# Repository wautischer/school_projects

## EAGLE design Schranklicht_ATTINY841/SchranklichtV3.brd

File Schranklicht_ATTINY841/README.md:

# Schranklicht
## Used Parts:
[partlist.txt](https://github.com/wautischer/Schranklicht/files/15400422/partlist.txt)
## Circuit:

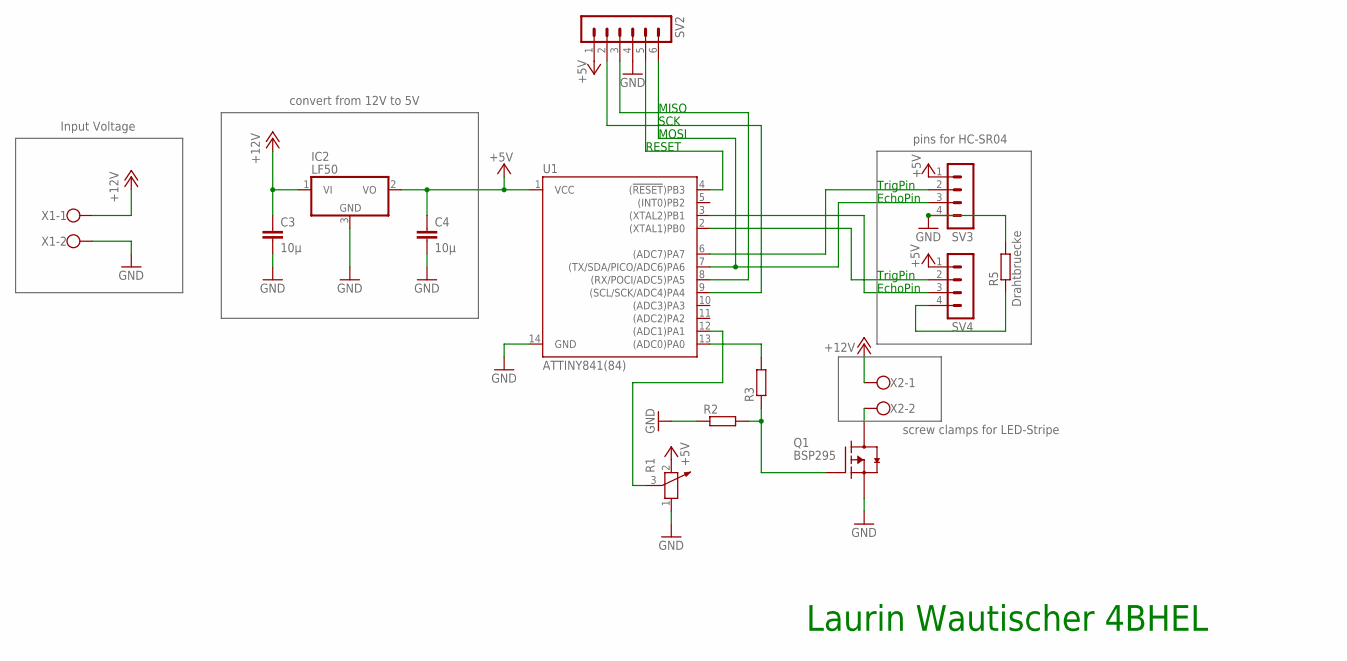
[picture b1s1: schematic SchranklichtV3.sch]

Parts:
C3, C4: 10µ; C1210
IC2: LF50; TO252
Q1: BSP295; SOT230P700X160-4N
R1: POTENTIOMETER_PT-10; PT-10
R2, R3: R-EU_0207/10; 0207/10
R5: Drahtbruecke; 0207/7
SV2: MA06-1
SV3, SV4: MA04-1
U1: ATTINY841(84); SO14
X1, X2: W237-102

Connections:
+5V: C4.1, IC2.2 (VO), R1.2, SV2.1, SV3.1, SV4.1, U1.1 (VCC)
+12V: C3.1, IC2.1 (VI), X1.1, X2.1
GND: C3.2, C4.2, IC2.3 (GND), Q1.3 (S), R1.1, R2.1, R5.2, SV2.4, SV3.4, U1.14 (GND), X1.2
unnamed: SV2.5, U1.4 ((!RESET!)PB3)
unnamed: SV2.6, SV3.3, U1.7 ((TX/SDA/PICO/ADC6)PA6)
unnamed: SV3.2, U1.6 ((ADC7)PA7)
unnamed: SV4.3, U1.3 ((XTAL2)PB1)
unnamed: SV4.2, U1.2 ((XTAL1)PB0)
unnamed: R1.3, U1.12 ((ADC1)PA1)
unnamed: R3.2, U1.13 ((ADC0)PA0)
unnamed: Q1.4 (D), X2.2
unnamed: Q1.1 (G), R2.2, R3.1
unnamed: R5.1, SV4.4
unnamed: SV2.2, U1.9 ((SCL/SCK/ADC4)PA4)
unnamed: SV2.3, U1.8 ((RX/POCI/ADC5)PA5)

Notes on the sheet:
Laurin Wautischer 4BHEL
Input Voltage
convert from 12V to 5V
pins for HC-SR04
screw clamps for LED-Stripe
RESET
MOSI
MISO
SCK
TrigPin
EchoPin

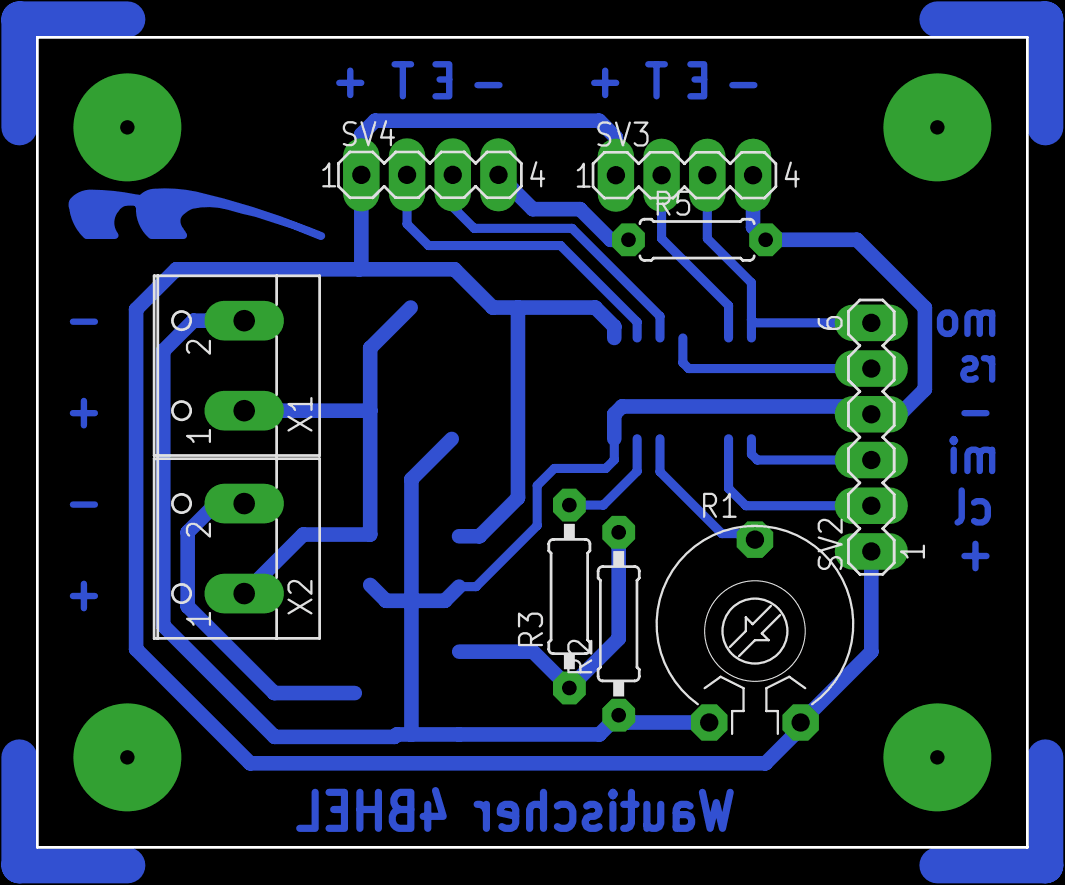
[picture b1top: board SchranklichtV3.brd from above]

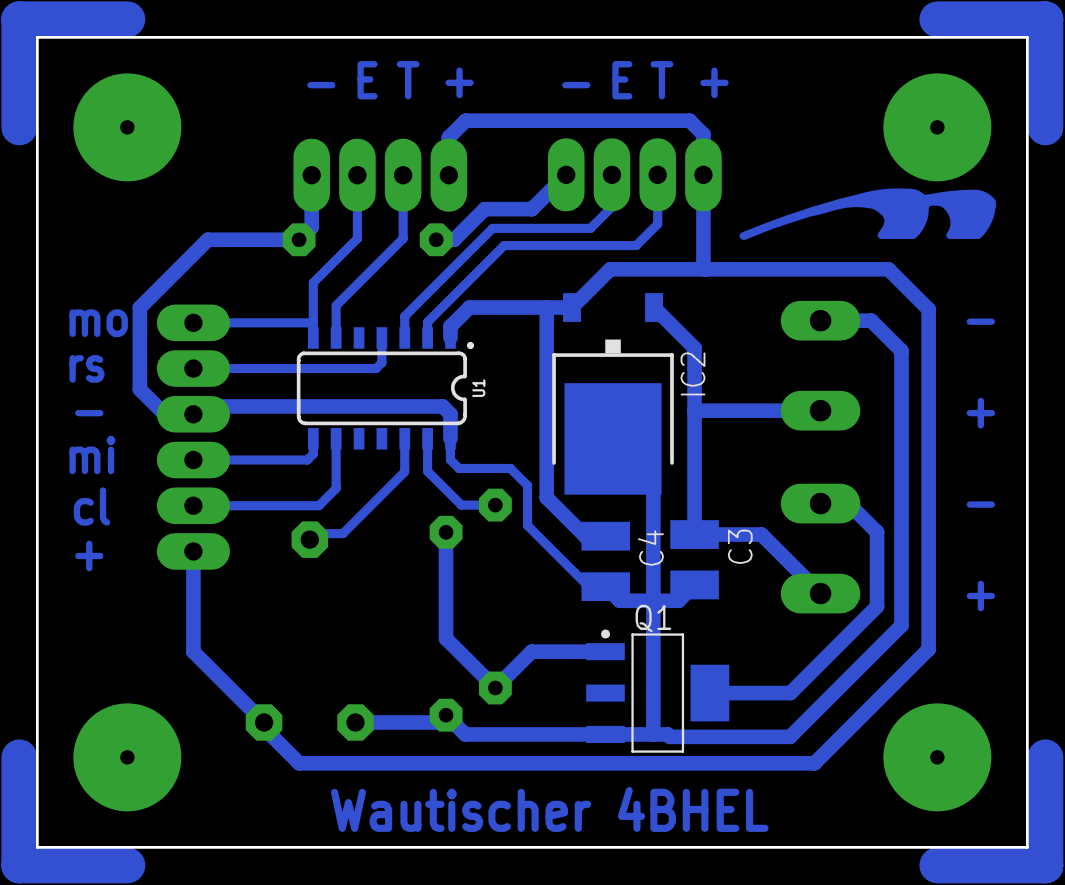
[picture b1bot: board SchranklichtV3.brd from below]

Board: 2 copper layers, 55.0 x 45.0 mm, 15 parts (5 on the bottom side), 15 nets.

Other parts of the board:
U$1: LOGOBOT_15

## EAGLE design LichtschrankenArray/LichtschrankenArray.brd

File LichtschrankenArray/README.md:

# LichtschrankenArray
## Used Parts
[partlist.txt](https://github.com/wautischer/LichtschrankenArray/files/11336794/partlist.txt)
## Circuit:

## Board:
### Top:

### Bottom:

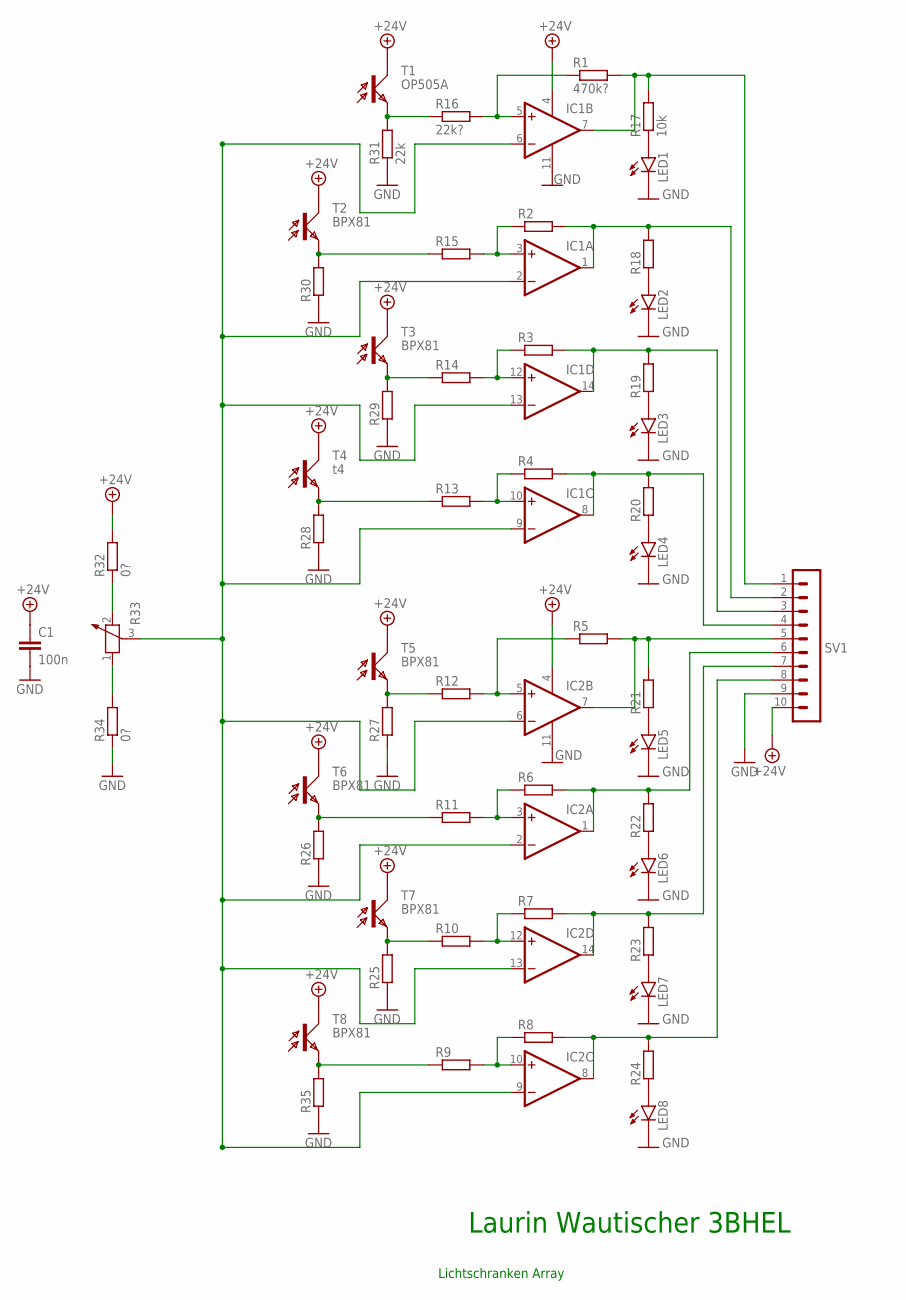
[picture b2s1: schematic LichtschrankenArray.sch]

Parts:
C1: 100n; C1206
IC1, IC2: 4AMP_P4+11N; DIL14
LED1, LED2, LED3, LED4, LED5, LED6, LED7, LED8: LEDSMT1206; 1206
R1: 470k?; 0207/10
R2, R3, R4, R5, R6, R7, R8, R18, R19, R20, R21, R22, R23, R24, R25, R26, R27, R28, R29, R30, R35: R-EU_0207/10; 0207/10
R9, R10, R11, R12, R13, R14, R15: R-EU_R1206; R1206
R16: 22k?; R1206
R17: 10k; 0207/10
R31: 22k; 0207/10
R32, R34: 0?; 0207/10
R33: POTENTIOMETER_PT-10; PT-10
SV1: MA10-1
T1: OP505A; BPX81
T2, T3, T5, T6, T7, T8: BPX81
T4: t4; BPX81

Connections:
+24V: C1.1, IC1.4 (V+), IC2.4 (V+), R32.2, SV1.10, T1.C, T2.C, T3.C, T4.C, T5.C, T6.C, T7.C, T8.C
GND: C1.2, IC1.11 (V-), IC2.11 (V-), LED1.C, LED2.C, LED3.C, LED4.C, LED5.C, LED6.C, LED7.C, LED8.C, R25.1, R26.1, R27.1, R28.1, R29.1, R30.1, R31.1, R34.1, R35.1, SV1.9
unnamed: IC1.5 (+IN), R1.1, R16.2
unnamed: IC2.5 (+IN), R5.1, R12.2
unnamed: IC1.7 (OUT), R1.2, R17.2, SV1.1
unnamed: LED1.A, R17.1
unnamed: LED2.A, R18.1
unnamed: IC1.3 (+IN), R2.1, R15.2
unnamed: IC1.1 (OUT), R2.2, R18.2, SV1.2
unnamed: LED3.A, R19.1
unnamed: IC1.12 (+IN), R3.1, R14.2
unnamed: IC1.14 (OUT), R3.2, R19.2, SV1.3
unnamed: LED4.A, R20.1
unnamed: IC1.10 (+IN), R4.1, R13.2
unnamed: IC1.8 (OUT), R4.2, R20.2, SV1.4
unnamed: LED5.A, R21.1
unnamed: LED6.A, R22.1
unnamed: IC2.3 (+IN), R6.1, R11.2
unnamed: IC2.1 (OUT), R6.2, R22.2, SV1.6
unnamed: LED7.A, R23.1
unnamed: IC2.12 (+IN), R7.1, R10.2
unnamed: IC2.14 (OUT), R7.2, R23.2, SV1.7
unnamed: LED8.A, R24.1
unnamed: IC2.10 (+IN), R8.1, R9.2
unnamed: IC2.8 (OUT), R8.2, R24.2, SV1.8
unnamed: IC2.7 (OUT), R5.2, R21.2, SV1.5
unnamed: R14.1, R29.2, T3.E
unnamed: R12.1, R27.2, T5.E
unnamed: R10.1, R25.2, T7.E
unnamed: R9.1, R35.2, T8.E
unnamed: R13.1, R28.2, T4.E
unnamed: R15.1, R30.2, T2.E
unnamed: R16.1, R31.2, T1.E
unnamed: IC1.2 (-IN), IC1.6 (-IN), IC1.9 (-IN), IC1.13 (-IN), IC2.2 (-IN), IC2.6 (-IN), IC2.9 (-IN), IC2.13 (-IN), R33.3
unnamed: R11.1, R26.2, T6.E
unnamed: R32.1, R33.2
unnamed: R33.1, R34.2

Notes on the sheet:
Lichtschranken Array
Laurin Wautischer 3BHEL

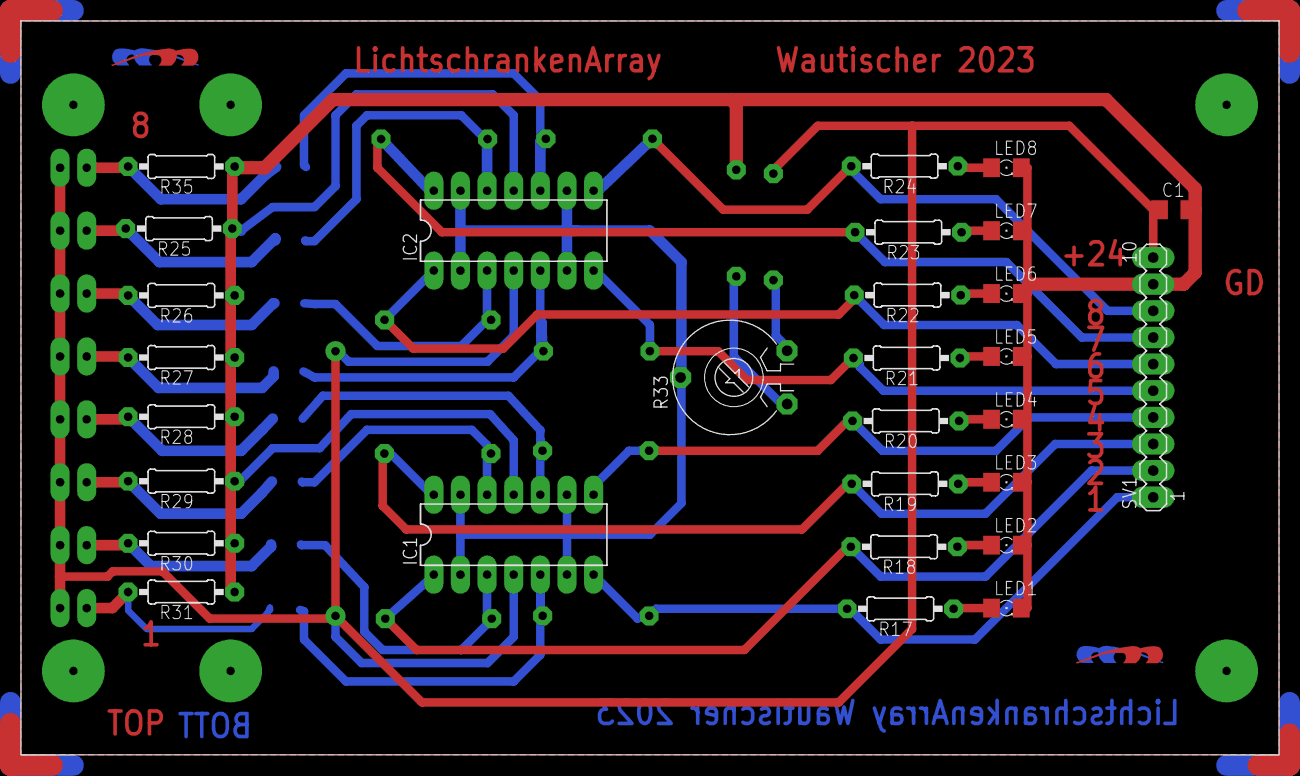
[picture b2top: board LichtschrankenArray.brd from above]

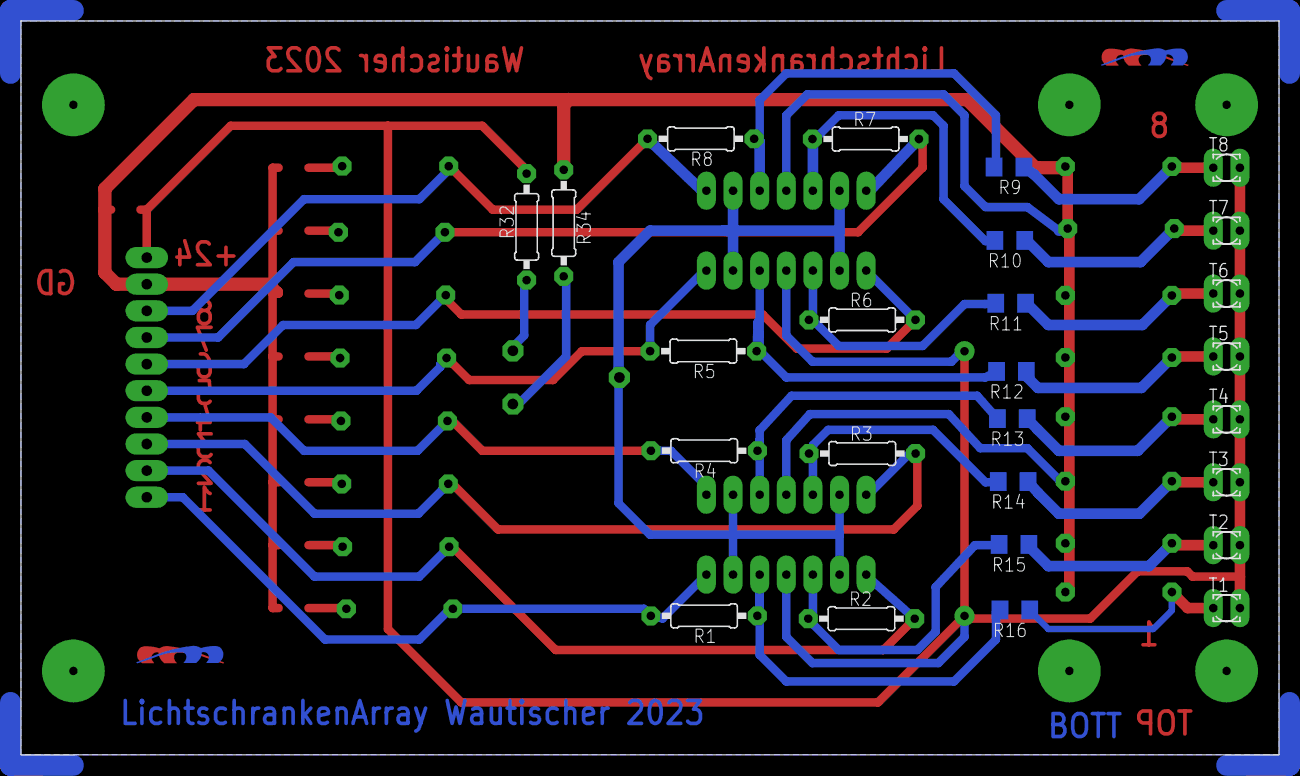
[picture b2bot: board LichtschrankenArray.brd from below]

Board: 2 copper layers, 120.0 x 70.0 mm, 57 parts (26 on the bottom side), 37 nets.

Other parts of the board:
U$1, U$2: HTL-LOGO

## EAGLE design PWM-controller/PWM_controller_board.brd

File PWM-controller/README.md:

# PWM-controller
## Used Parts:
[Partlist.txt](https://github.com/wautischer/PWM-controller/files/9204236/Partlist.txt)

## Circuit:

## Board:

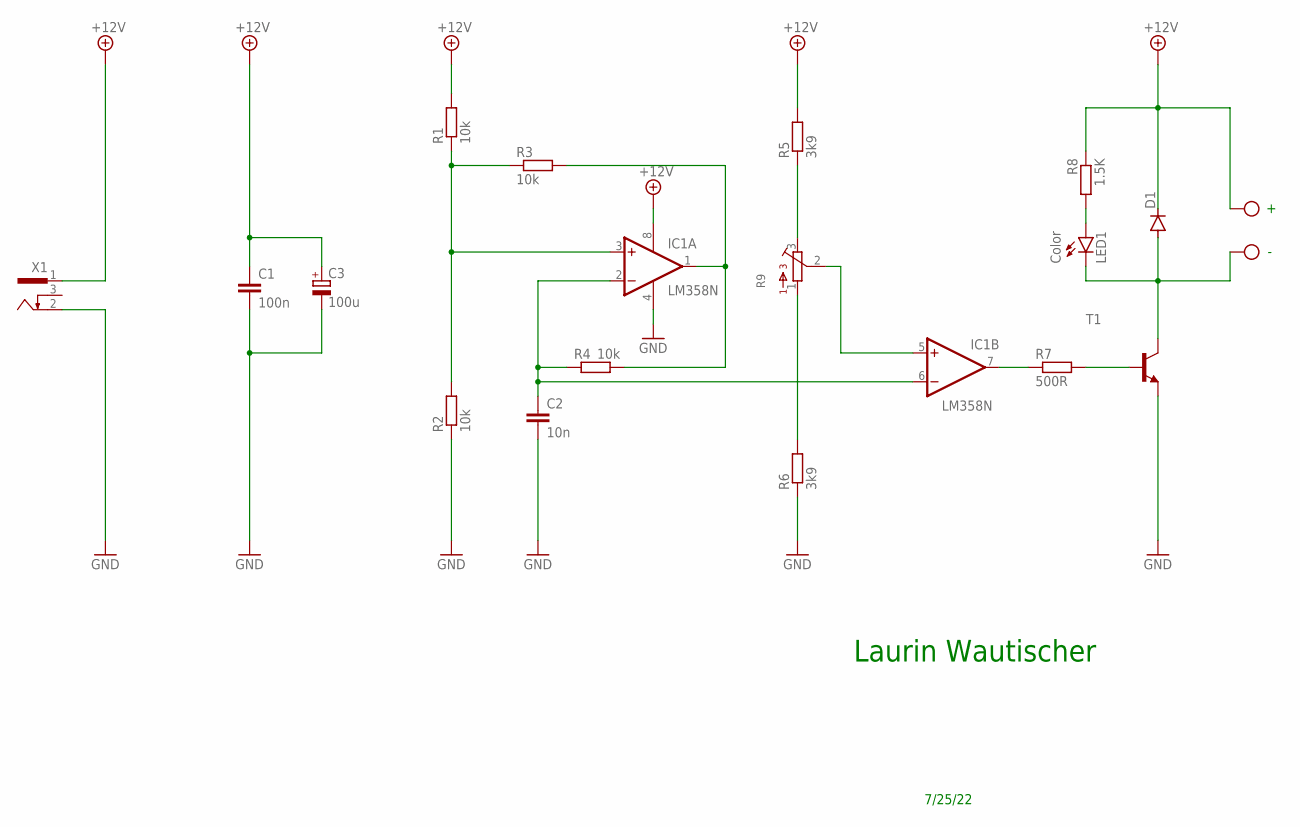
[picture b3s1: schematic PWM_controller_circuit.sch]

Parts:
C1: 100n; C050-030X075
C2: 10n; C050-030X075
C3: 100u; E5-6
D1: 1N4004; DO41-10
IC1: LM358N; DIL08
LED1: Color; LED3MM
R1, R2, R3, R4: 10k; 0207/10
R5, R6: 3k9; 0207/10
R7: 500R; 0207/10
R8: 1.5K; 0207/10
R9: 3386-F; 3386F
T1: BC639-NPN-TO92-ECB; TO92-ECB
X1: 733980-62
X2: MKDSN1,5/2-5,08

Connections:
+12V: C1.1, C3.+, D1.C, IC1.8 (V+), R1.2, R5.2, R8.1, X1.1, X2.2
GND: C1.2, C2.2, C3.-, IC1.4 (V-), R2.1, R6.1, T1.E, X1.2
unnamed: IC1.3 (+IN), R1.1, R2.2, R3.1
unnamed: C2.1, IC1.2 (-IN), IC1.6 (-IN), R4.1
unnamed: IC1.1 (OUT), R3.2, R4.2
unnamed: R6.2, R9.1
unnamed: IC1.7 (OUT), R7.1
unnamed: R7.2, T1.B
unnamed: D1.A, LED1.K (C), T1.C, X2.1
unnamed: IC1.5 (+IN), R9.2
unnamed: R5.1, R9.3
unnamed: LED1.A, R8.2

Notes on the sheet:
7/25/22
Laurin Wautischer

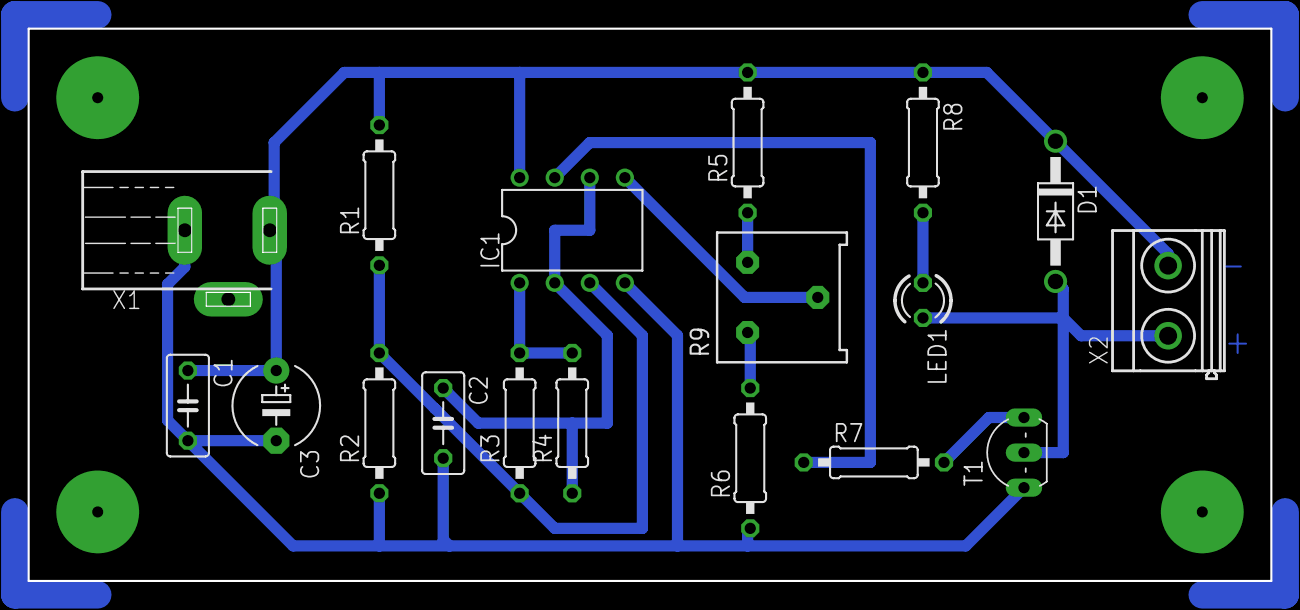
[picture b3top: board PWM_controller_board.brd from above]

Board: 2 copper layers, 90.0 x 40.0 mm, 18 parts (0 on the bottom side), 12 nets.

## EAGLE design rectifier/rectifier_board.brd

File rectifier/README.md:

# Rectifier
## Used Parts:
[partlist.txt](https://github.com/wautischer/rectifier/files/9220773/partlist.txt)

## Circuit:

## Board:

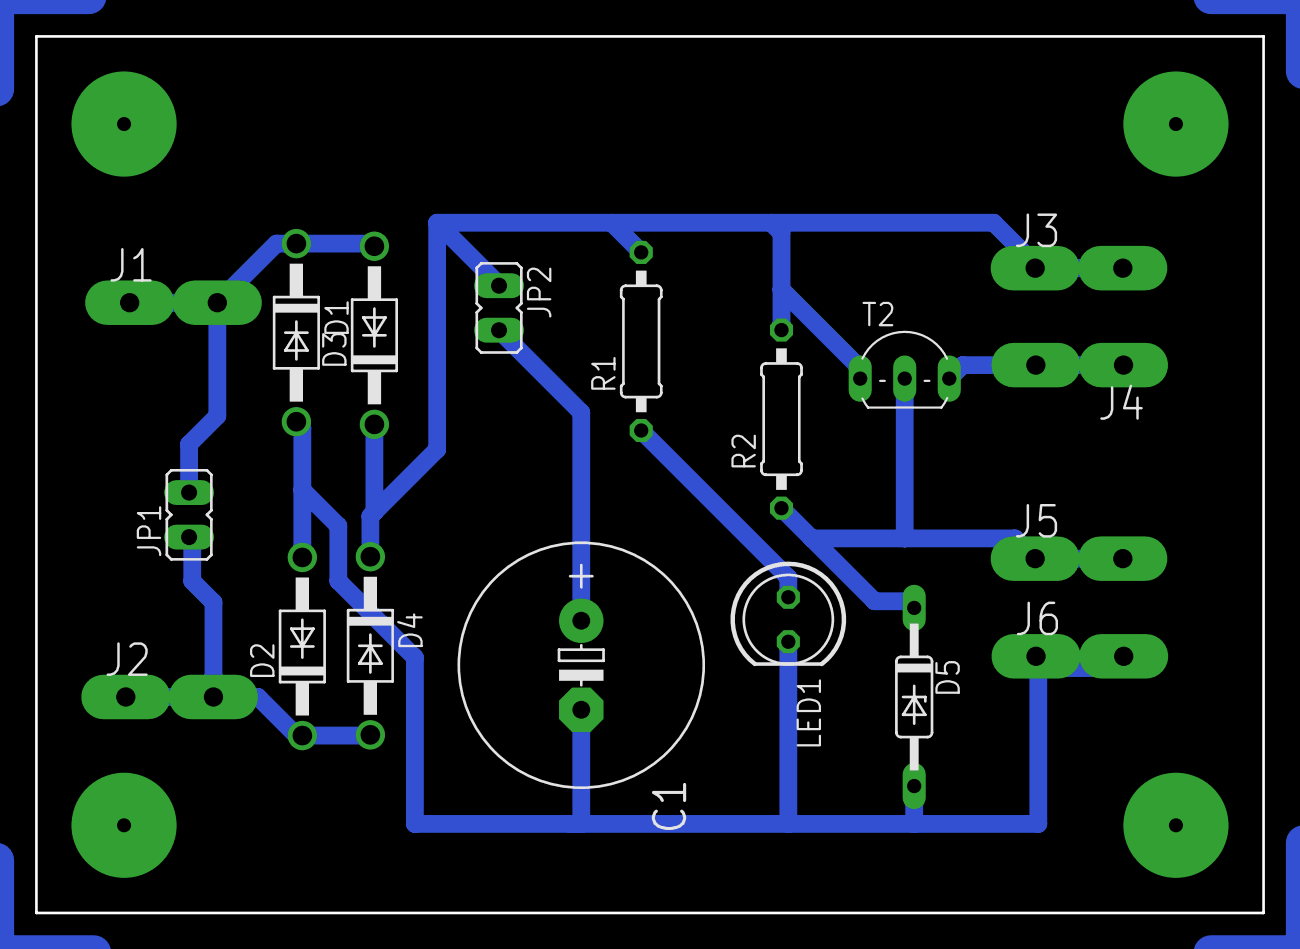
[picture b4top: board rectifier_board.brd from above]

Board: 2 copper layers, 70.0 x 50.0 mm, 18 parts (0 on the bottom side), 8 nets.

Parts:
C1: 330 mikro; E5-13
D1, D2, D3, D4: 1N4004; DO41-10
D5: DO35Z10
J1, J2, J3, J4, J5, J6: PIN2F061.080; F061.080
JP1, JP2: JP1
LED1: LED5MM
R1: 1kOhm; 0207/10
R2: 680Ohm; 0207/10
T2: 330mikro; TO92-CBE

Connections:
unnamed: D1.C, D3.A, J1.1A, J1.1B, JP1.2
unnamed: LED1.A, R1.1
unnamed: D2.C, D4.A, J2.1A, J2.1B, JP1.1
unnamed: C1.+, JP2.2
unnamed: C1.-, D1.A, D2.A, D5.A, J6.1A, J6.1B, LED1.K
unnamed: D5.C, J5.1A, J5.1B, R2.1, T2.B
unnamed: J4.1A, J4.1B, T2.E
unnamed: D3.C, D4.C, J3.1A, J3.1B, JP2.1, R1.2, R2.2, T2.C

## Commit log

2025-07-01 add project
2025-07-01 add projects from 2021-2025
2025-07-01 update agarSingelplayer

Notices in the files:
parts and their libraries:
SparkFun-IC-Microcontroller: Licensing: Creative Commons ShareAlike 4.0 International - https://creativecommons.org/licenses/by-sa/4.0
